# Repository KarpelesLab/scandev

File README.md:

# scandev

A self-contained nuclear quadrupole resonance (NQR) spectrometer: put a
sample in a coil, send a short radio-frequency pulse, and listen for the
faint signal the nuclei send back. The frequency of that signal identifies
the compound, through a sealed container and with no magnet.

The project follows Applied Science's video
[Identify chemicals with radio frequencies - Nuclear Quadrupole Resonance (MRI without magnets)](https://www.youtube.com/watch?v=JO_EHceV9sk),
which builds one around an oscilloscope, a bench amplifier and a passive
transmit/receive network. Here the oscilloscope is replaced by an FPGA, an
ADC and purpose-built boards.

## Status

Early. Nothing has been built or run on hardware yet.

| Part | State |
|------|-------|
| Probe and pulse numbers (`sim/probe.py`) | done |
| Transmit/receive front end in SPICE (`sim/frontend.py`) | passive network modelled |
| Amplifier output network (`sim/pa.py`) | done |
| Schematics of the four boards (`hw/`) | written; KiCad's netlist matches and the rule check passes |
| Layout of the four boards | placed and autorouted; no rule violations, nothing unconnected; not reviewed |
| Parts | every catalogue number checked against JLCPCB; only the SMA connectors and the probe's hand-fitted parts are not chosen |
| Fabrication files (`hw/lib/fab.py`) | generated for all four boards; placement rotations unchecked |
| Gateware core (`gateware/rtl`) | passes simulation, synthesises for `xc7a35t-ftg256`; on hold until a board exists |
| RP2040 firmware, host software | not started |

## Boards

Four boards joined by SMA cables. Each is a pair of Python scripts in
`hw/`: one writes the KiCad schematic, a PDF of it and a BOM, and checks
KiCad's reading of the netlist against the script; the other places the
footprints, routes the board and runs the design rule check.

- **Digital** (`hw/dig`): Xilinx Artix-7 (XC7A35T-FTG256) and an AD9226
  12-bit ADC on one 50 MHz oscillator. An RP2040 with its own USB-C port,
  BOOTSEL and reset buttons loads the FPGA (there is no configuration
  flash) and keeps bitstreams and scan results on a microSD card.
- **Amplifier** (`hw/pa`): a half-bridge switching at the carrier, 3.8 W
  at 12 V into 50 ohm. It is silent when it is not switching, and its rail
  collapses if it is left transmitting. Takes the 12 V input for the system.
- **Receive front end** (`hw/fe`): series crossed diodes towards the
  amplifier, three quarter-wave sections with shunt diodes towards the
  receiver, two low-noise stages with a blanking switch between them.
- **Probe** (`hw/probe`): the tuning and matching capacitors for the
  sample coil, 1 kV parts with pads for hand-fitted variable capacitors,
  and a thermistor for the sample's temperature. Goes in a shielded box
  with the coil.

The amplifier's output network and the front end's quarter-wave sections
are fitted to one frequency. They are fitted for hexamine.

Renders of the current layouts (KiCad's 3D view; parts without a 3D model
in KiCad's library, the FPGA among them, are missing):

| | |
|---|---|
|  Digital |  Amplifier |
|  Receive front end |  Probe |

### Wiring

| From | To | Cable |
|------|----|-------|
| digital `TX HI`, `TX LO` | amplifier `HI IN`, `LO IN` | SMA |
| digital `PA EN` | amplifier `EN` | 2-pin |
| amplifier `TX OUT` | front end `TX IN` | SMA |
| front end `PROBE` | probe `TO FRONT END` | SMA |
| front end `RX OUT` | digital `RX IN` | SMA |
| digital `BLANK` | front end `PWR/BLANK` pins 3-4 | 2-pin |
| amplifier `12V OUT A` | front end `PWR/BLANK` pins 1-2 | 2-pin |
| amplifier `12V OUT B` | digital `12V IN` | 2-pin |
| probe `TEMP` | digital `TEMP` | 2-pin |

The digital board's logic runs from its USB port; 12 V only feeds its ADC.

### Known weak points

- The layouts are autorouted first passes. Nobody has looked at the
  amplifier feedback loops, return paths or the FPGA's supply routing.
- The OPA855 stages are fast enough to oscillate on a careless layout.
- The gateware drives the two bridge inputs as exact complements. The
  driver blocks both-on but adds no dead time; the gateware should.
- The FPGA's supplies come up in no particular order.
- The ADC's 5 V regulator drops 7 V at about 100 mA and will run warm.

## Samples

The video's sodium nitrite is not something to buy casually, so the first
target is **hexamine** (solid camping-fuel tablets): a nitrogen line at
3.306 MHz at room temperature whose signal lasts about 1.5 ms, long enough
that the receiver's dead time after the pulse costs little.

## Layout

```
sim/        design numbers and the ngspice front-end model
hw/         board scripts, generated schematics, PDFs and BOMs
gateware/   Verilog (rtl/), testbench and its Python judge (tb/)
video/      script used to transcribe the reference video for study
```

## Running the checks

```sh
python3 sim/probe.py          # coil, matching, pulse length, ring-down
python3 sim/frontend.py       # needs ngspice
python3 gateware/tb/run_core.py
python3 hw/fe/fe.py           # schematic; likewise pa, dig, probe; needs KiCad 9+
python3 hw/fe/fe_pcb.py --route   # layout; needs freerouting under tools/
python3 hw/lib/checkbom.py hw/*/*-bom.csv
python3 hw/lib/fab.py fe pa probe dig
```

The gateware is simulated and synthesised with
[reticle](https://github.com/KarpelesLab/reticle). `run_core.py` looks for
the binary at `tools/reticle-target/release/reticle`, or wherever the
`RETICLE` environment variable points.

## Safety

The probe coil and the probe board carry several hundred volts of RF
during a pulse. Sodium
nitrite is toxic in gram quantities: keep it in a sealed tube.

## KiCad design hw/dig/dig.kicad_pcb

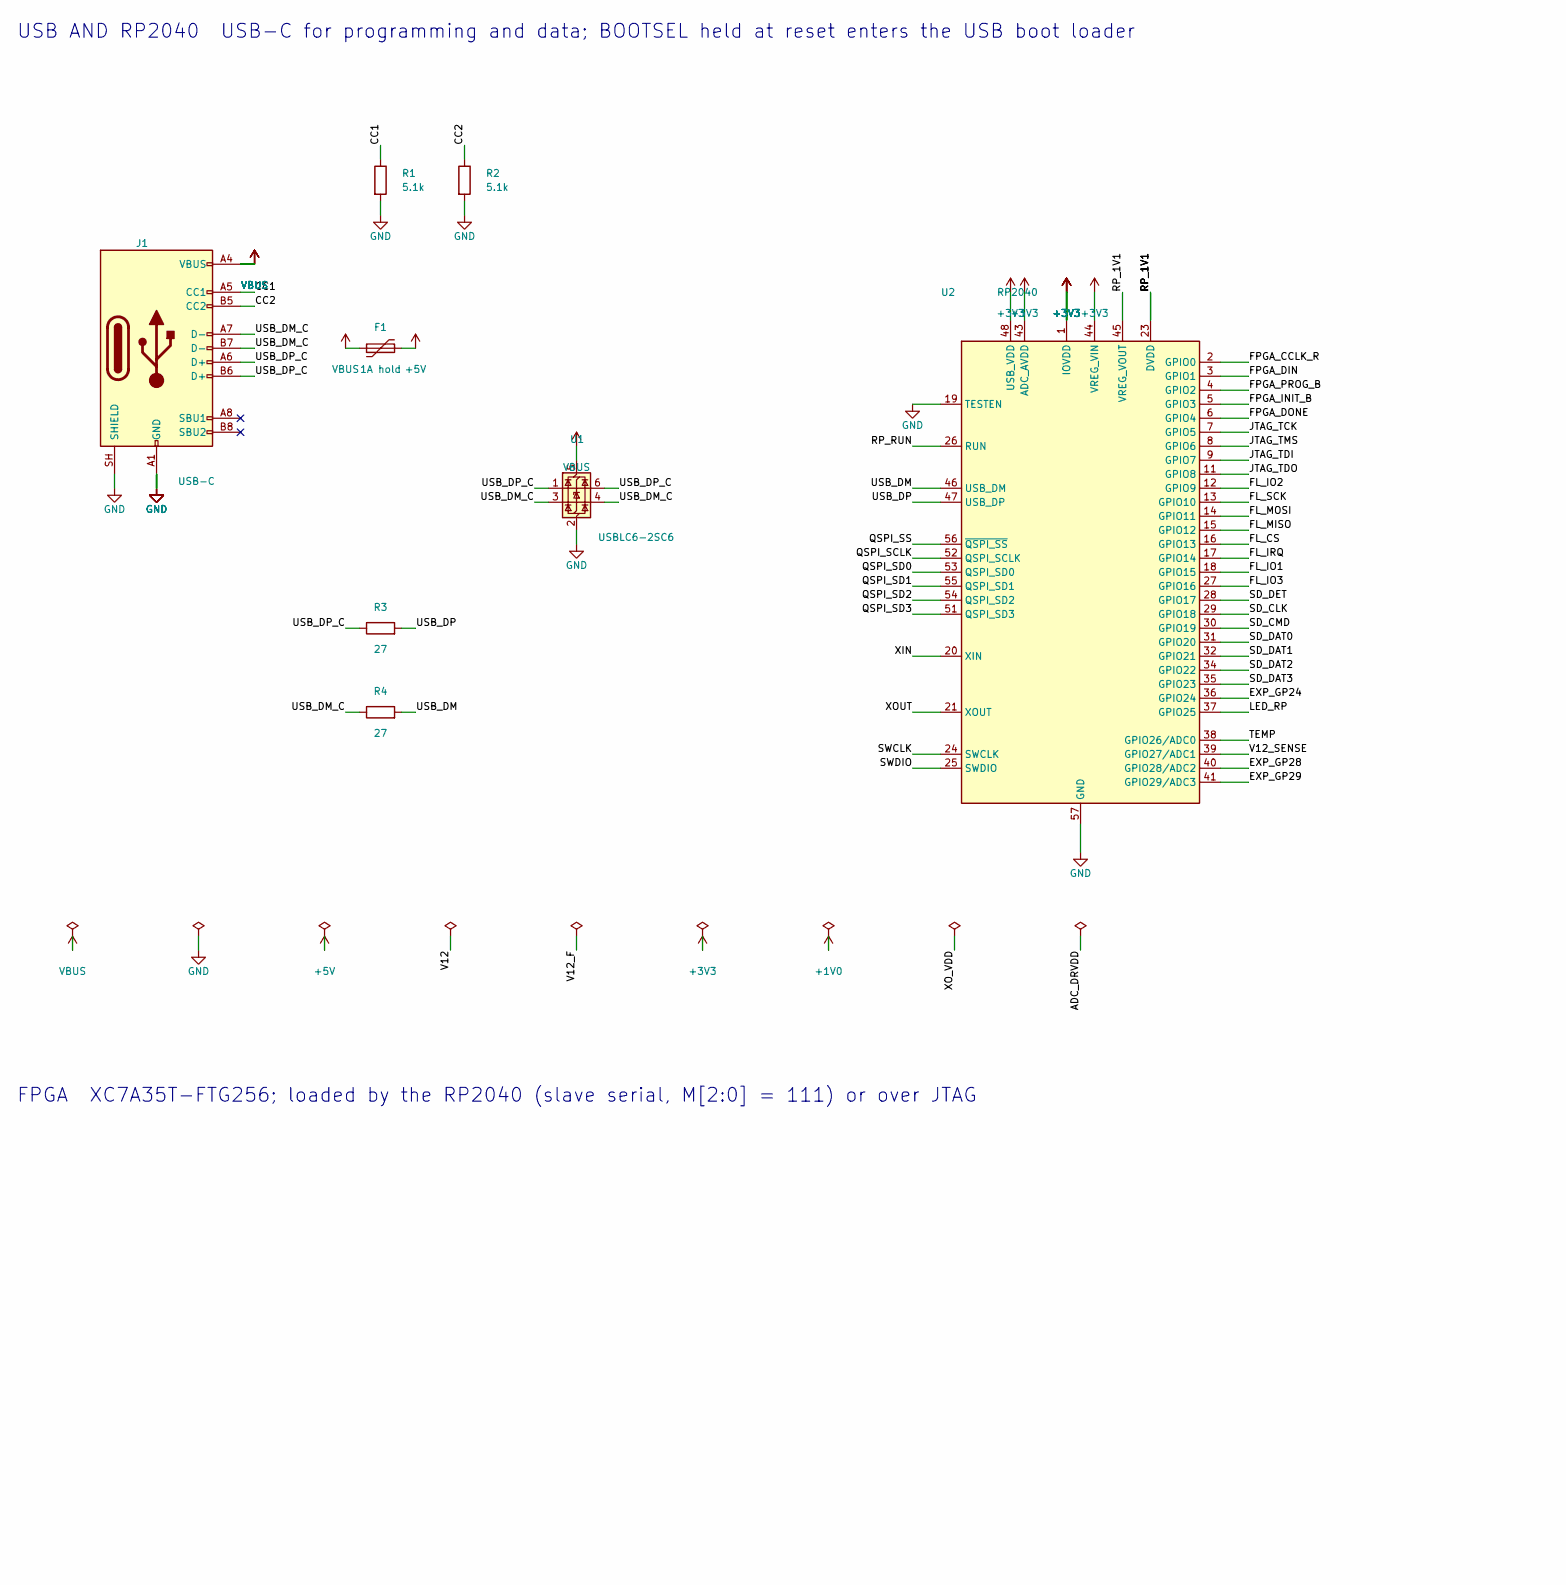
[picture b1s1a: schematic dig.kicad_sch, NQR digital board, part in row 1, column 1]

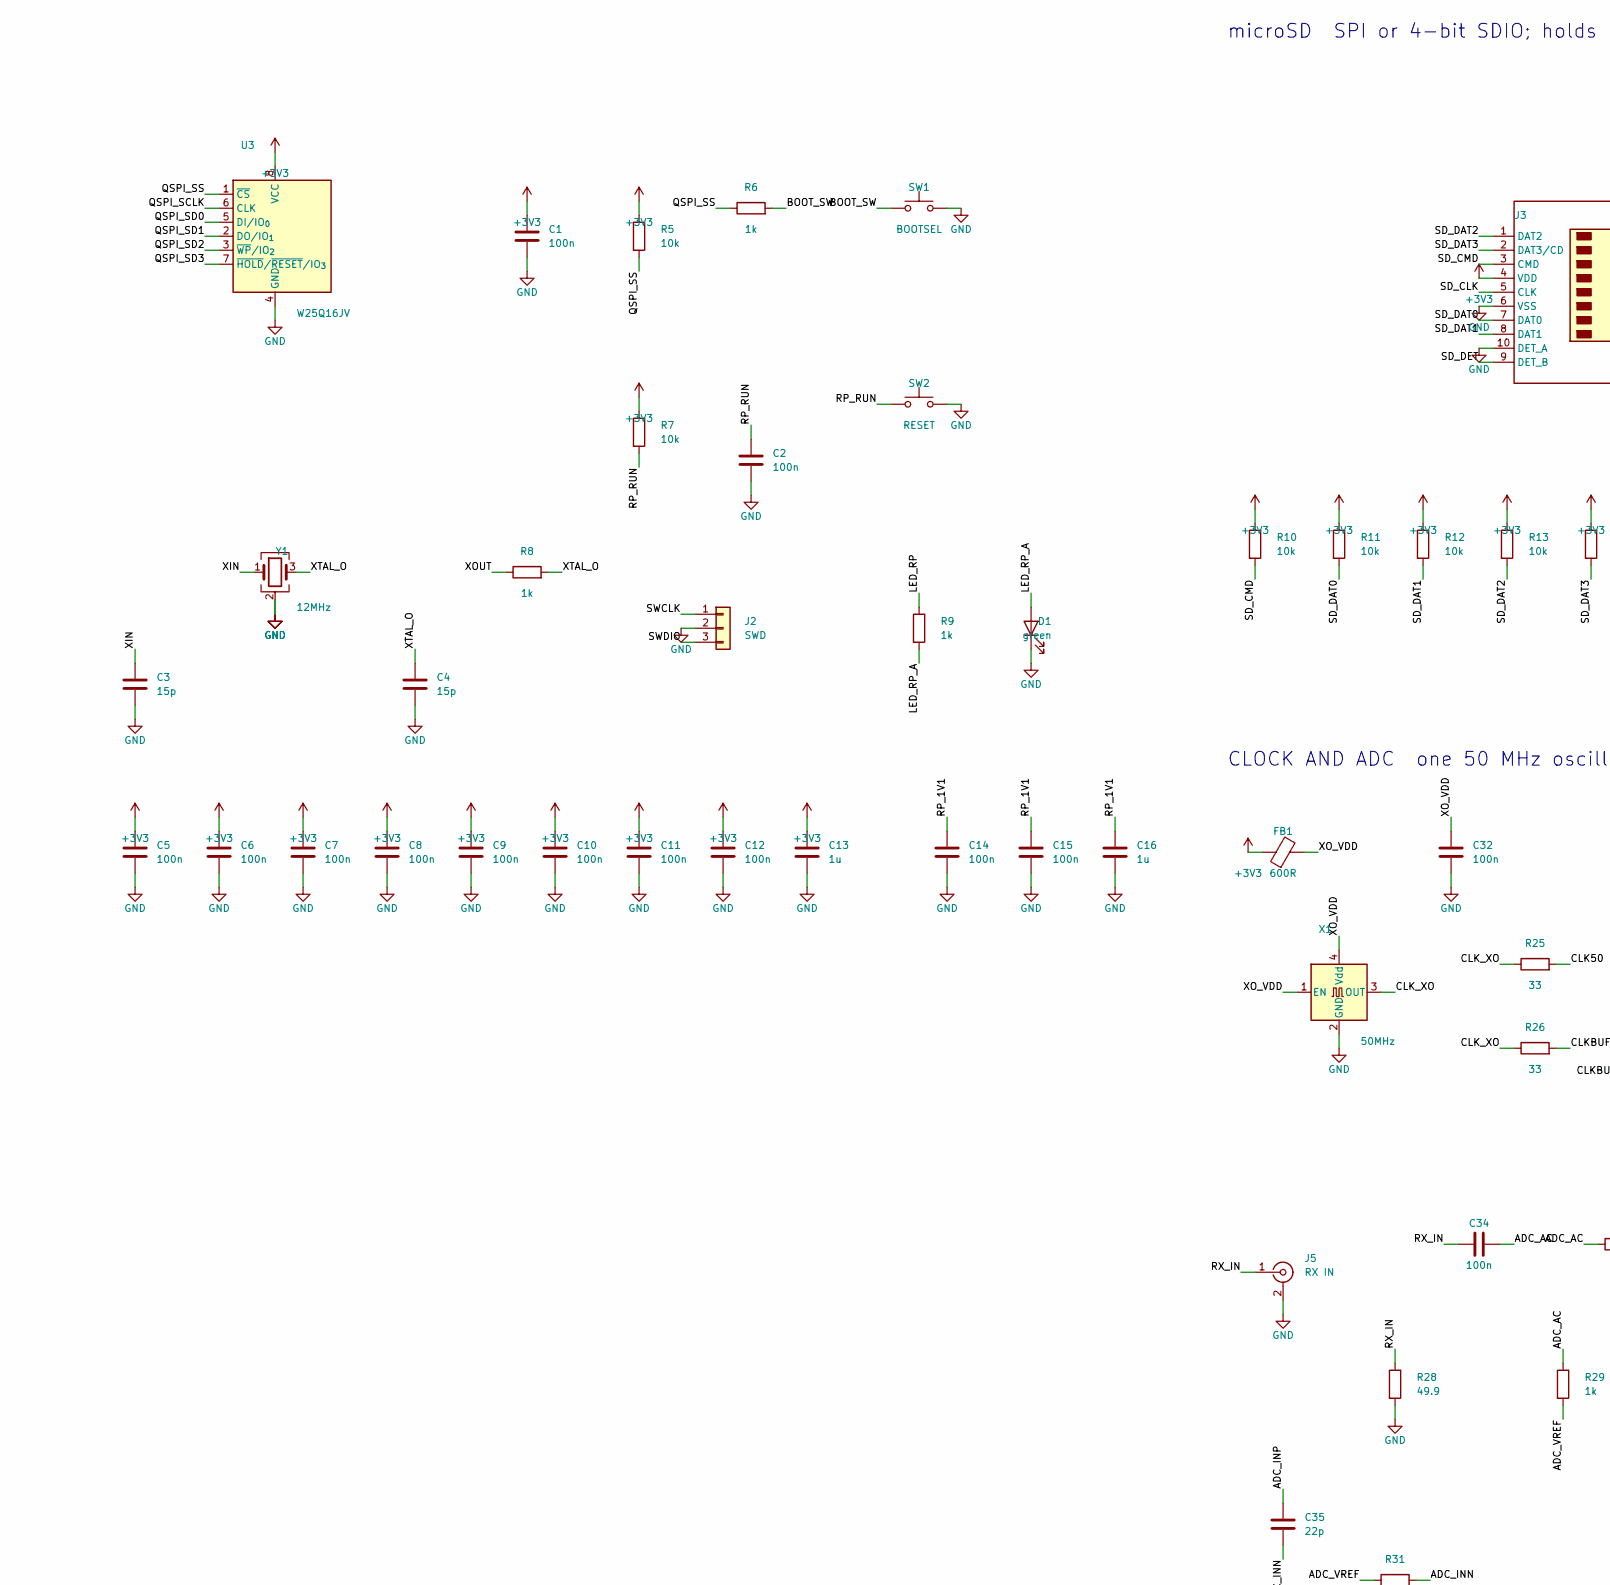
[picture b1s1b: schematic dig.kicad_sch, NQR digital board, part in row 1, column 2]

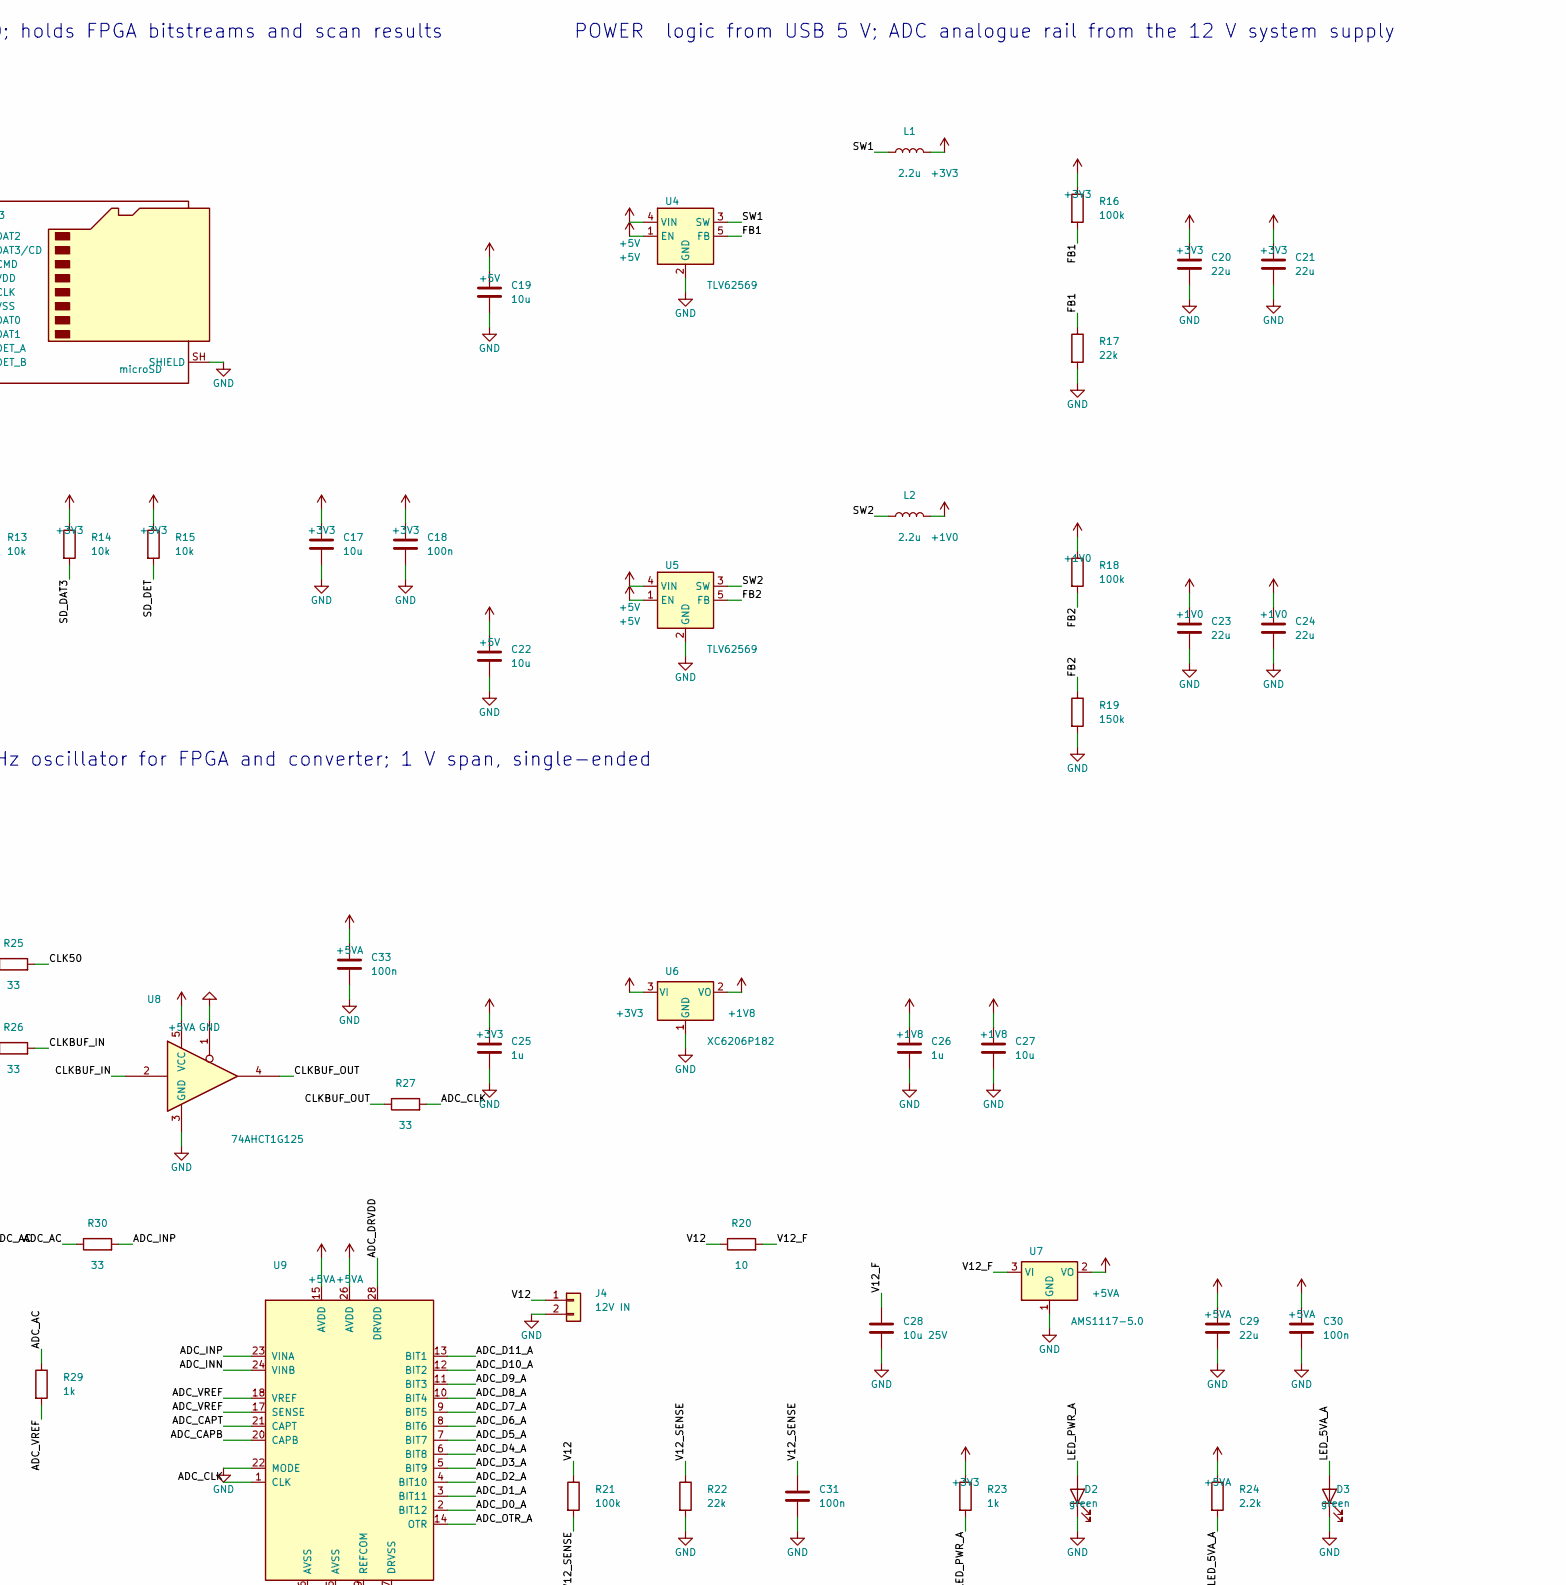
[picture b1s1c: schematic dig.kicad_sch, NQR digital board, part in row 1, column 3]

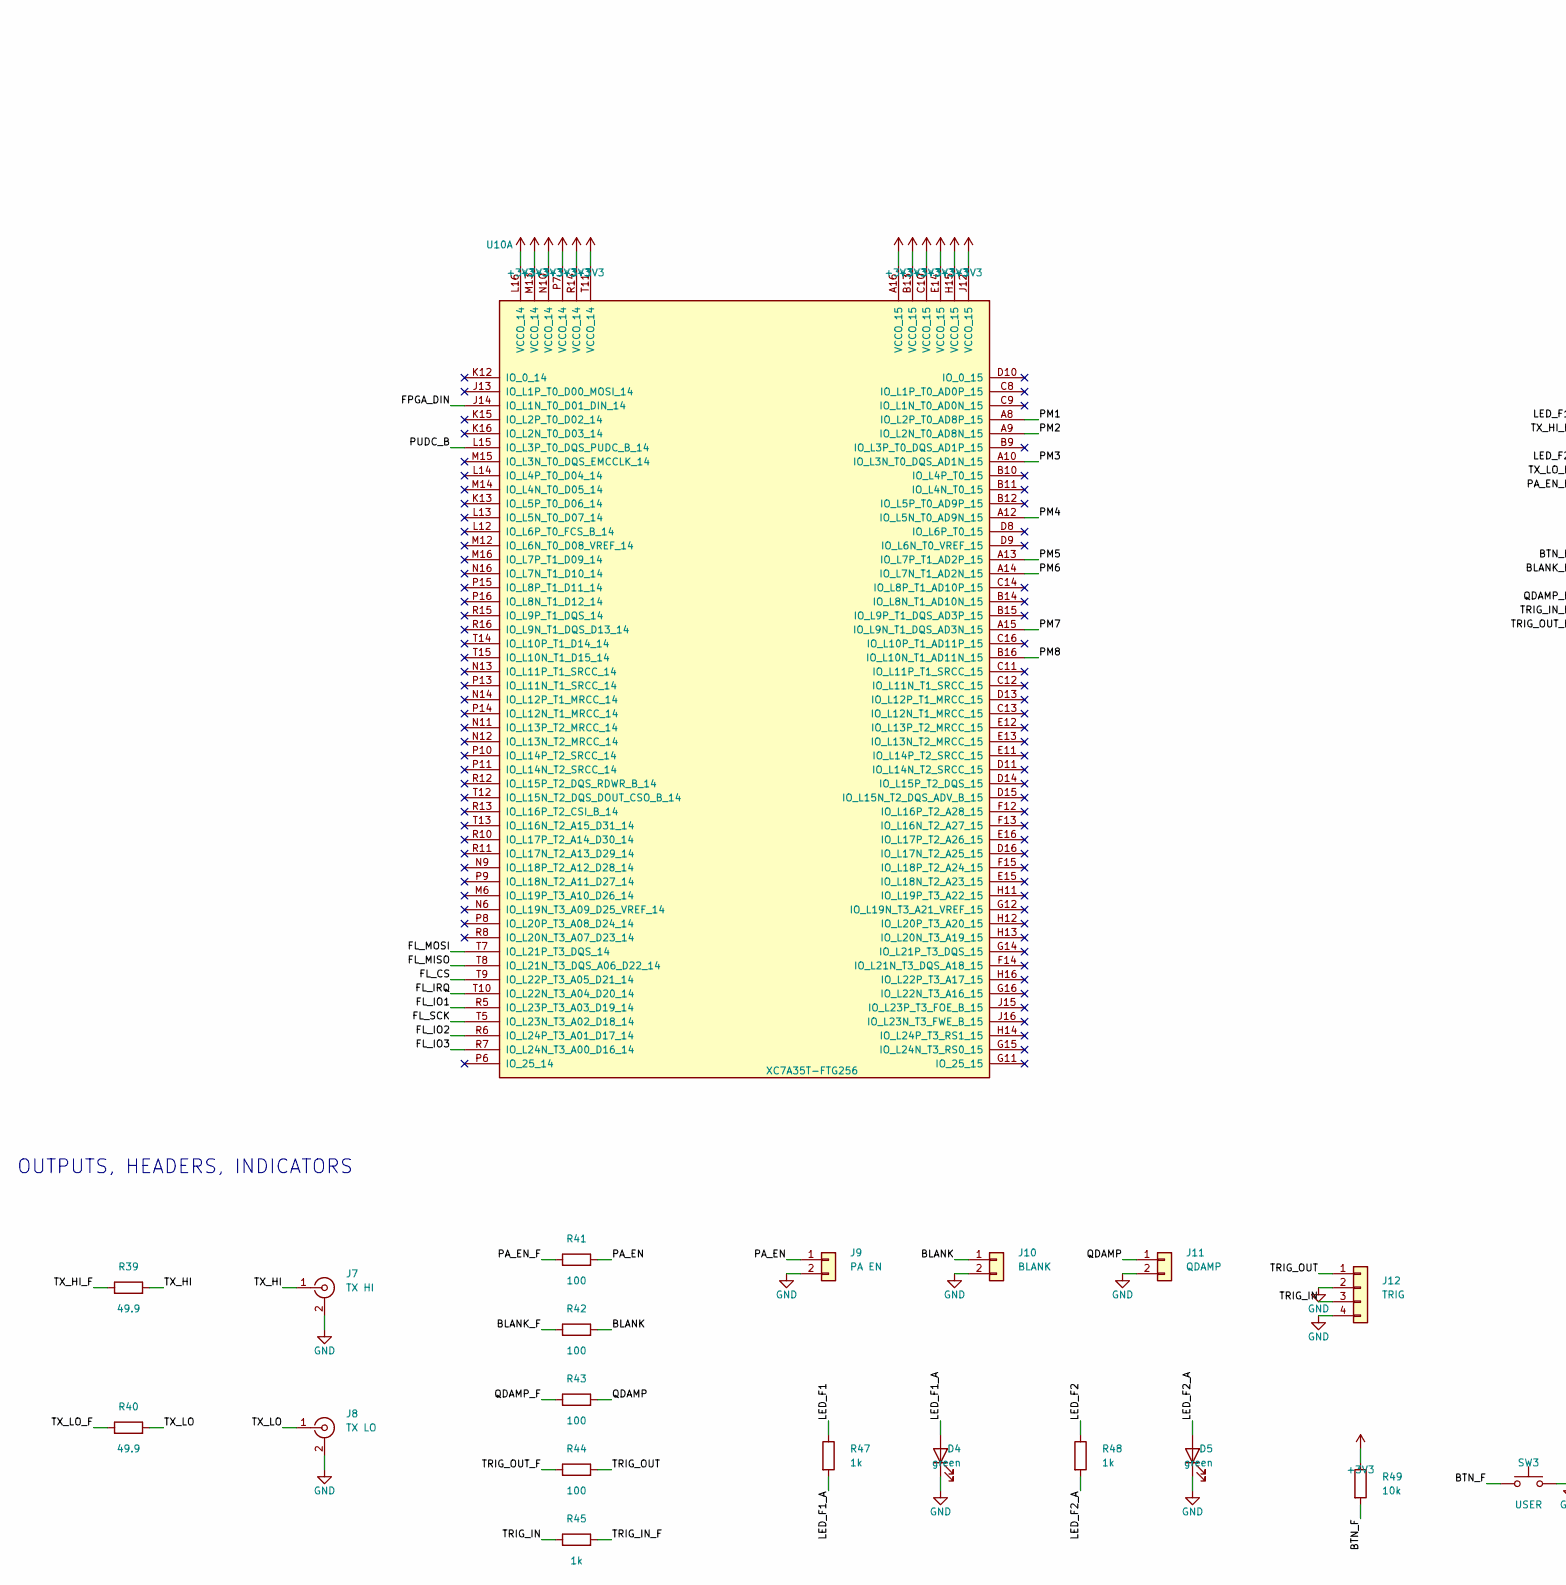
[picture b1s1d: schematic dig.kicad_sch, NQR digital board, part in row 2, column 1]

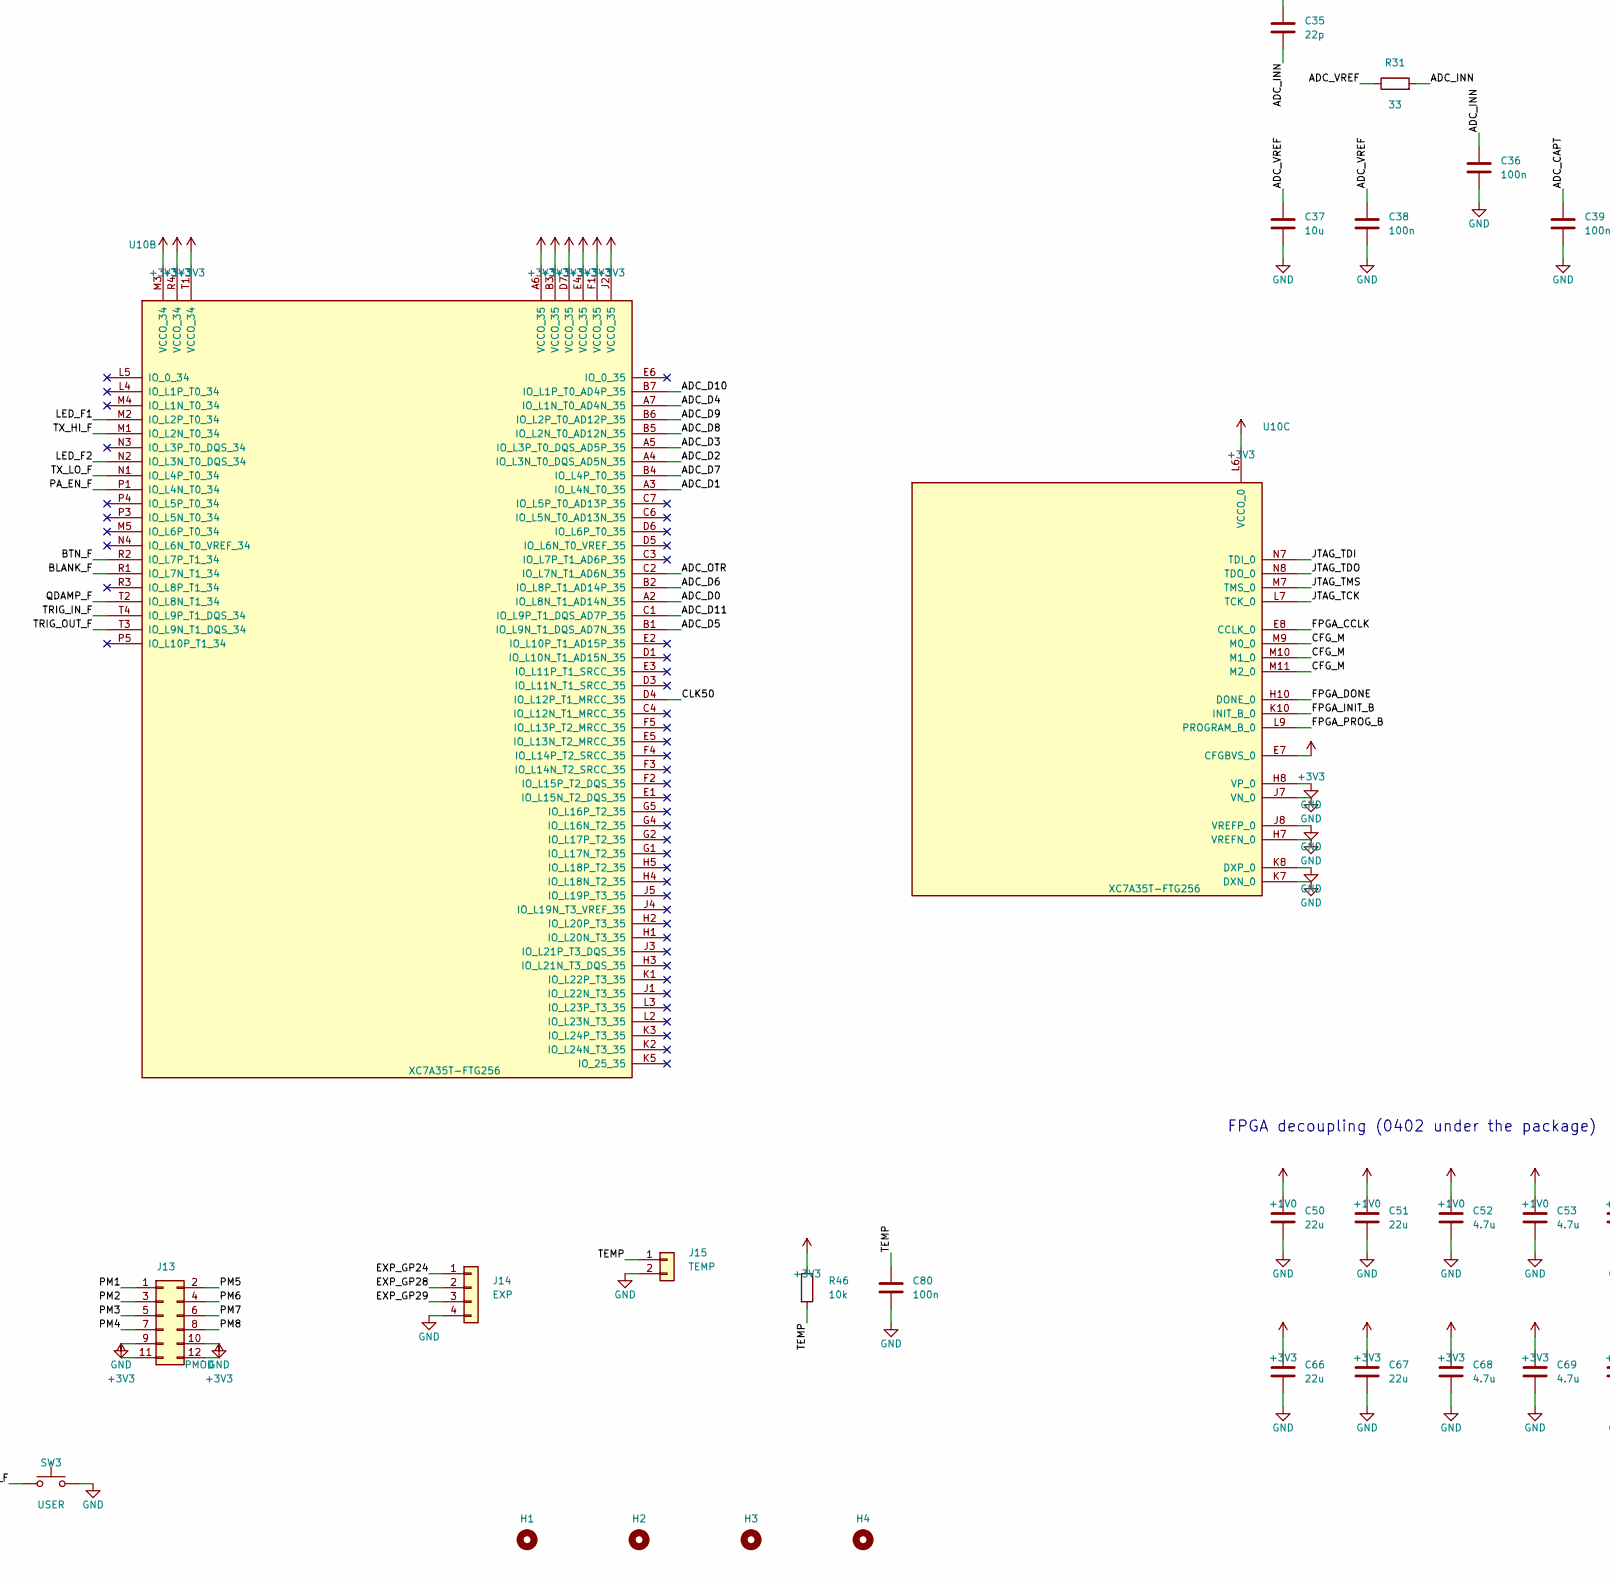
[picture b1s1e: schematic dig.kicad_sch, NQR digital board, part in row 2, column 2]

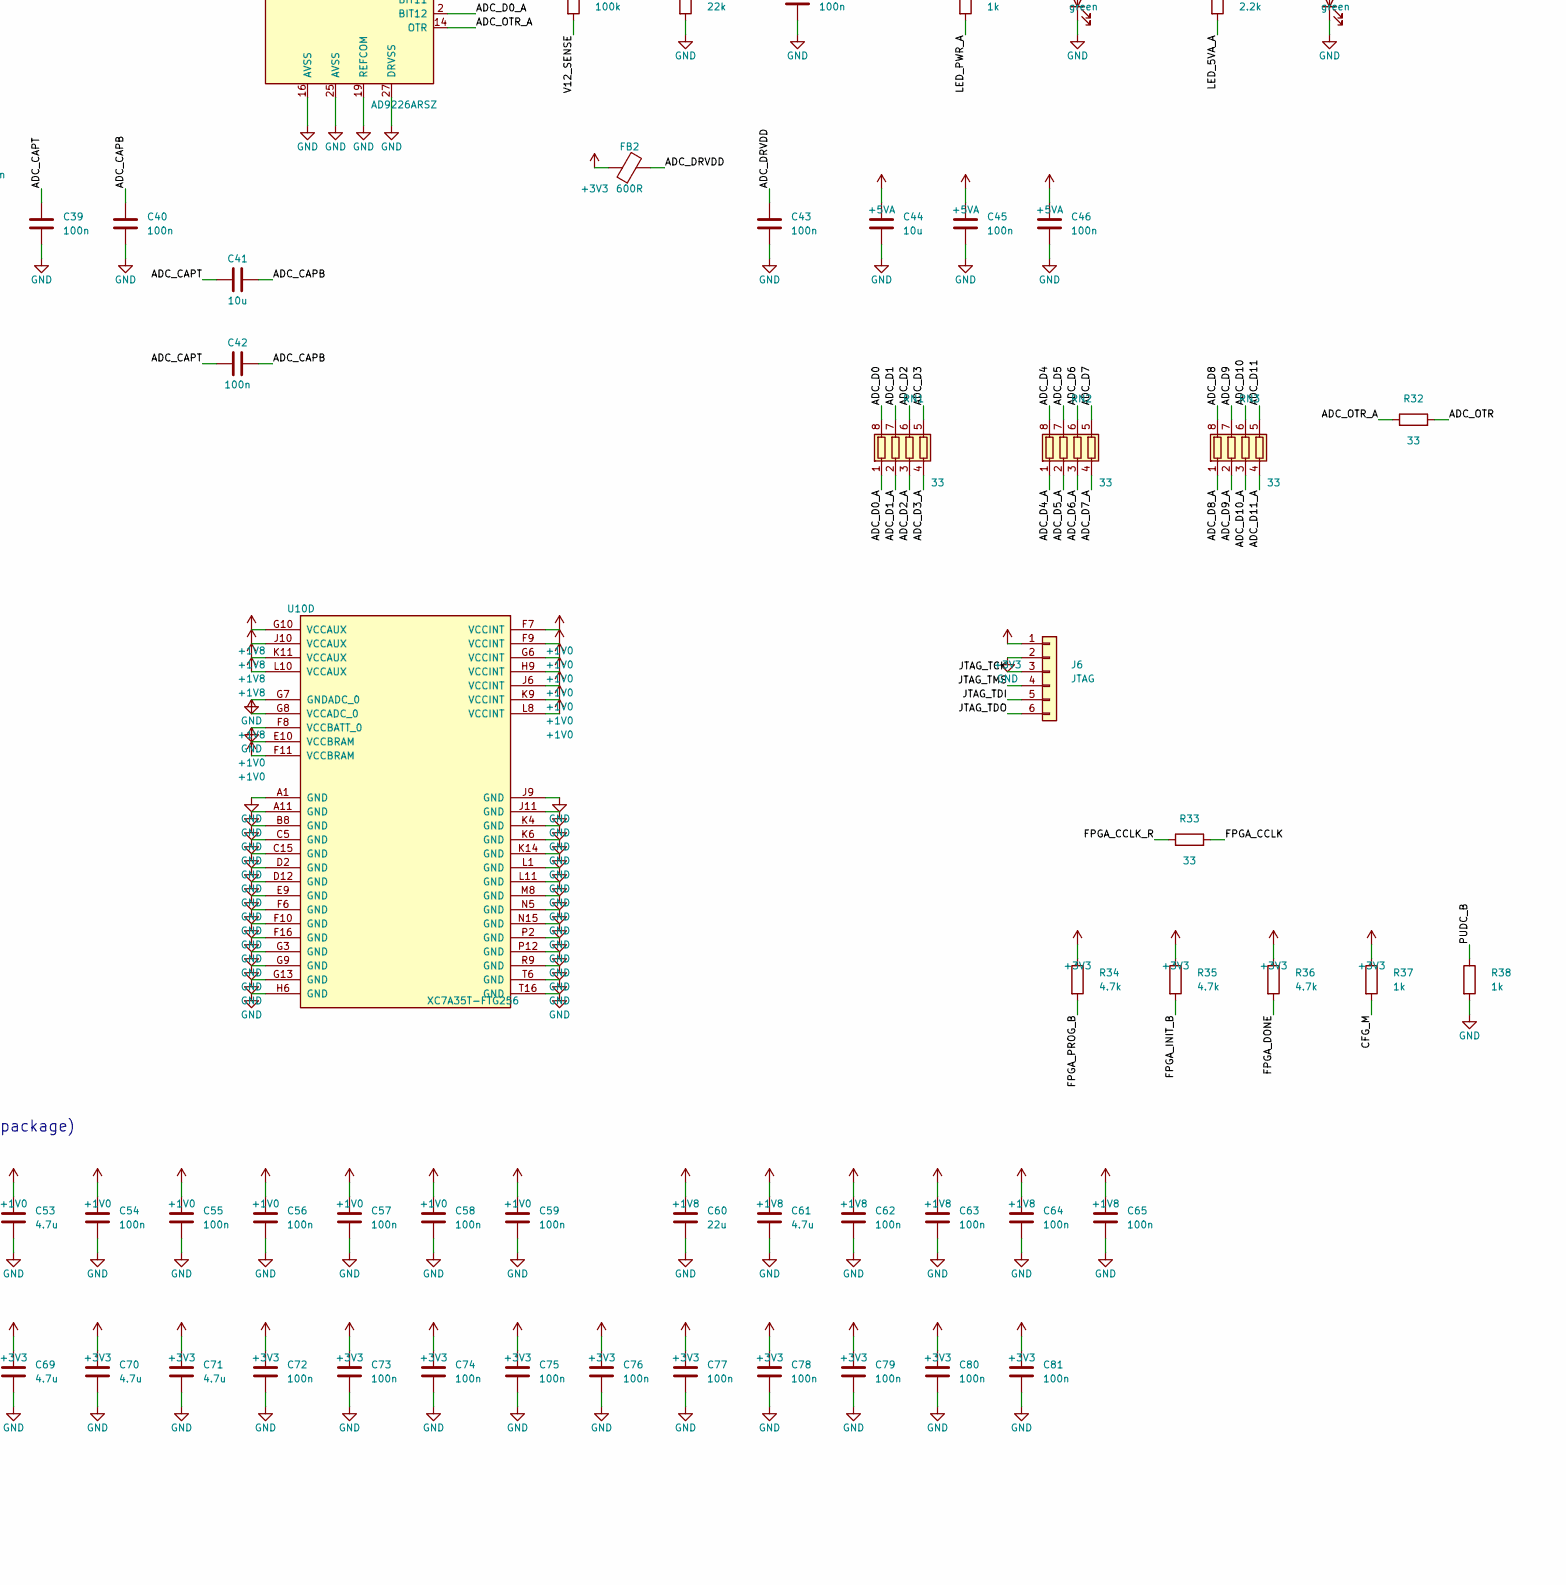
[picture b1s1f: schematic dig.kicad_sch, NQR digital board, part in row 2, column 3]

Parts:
C1, C2, C5, C6, C7, C8, C9, C10, C11, C12, C14, C15, C18, C30, C31, C32, C33, C34, C36, C38, C39, C40, C42, C43, C45, C46: 100n; C_0603_1608Metric; LCSC C14663
C3, C4: 15p; C_0603_1608Metric; LCSC C107037
C13, C16, C25, C26: 1u; C_0603_1608Metric; LCSC C15849
C17, C19, C22, C27, C37, C41, C44: 10u; C_0805_2012Metric; LCSC C15850
C20, C21, C23, C24, C29, C50, C51, C60, C66, C67: 22u; C_0805_2012Metric; LCSC C98190
C28: 10u 25V; C_1206_3216Metric; LCSC C9807
C35: 22p; C_0603_1608Metric; LCSC C525244
C52, C53, C61, C68, C69, C70, C71: 4.7u; C_0805_2012Metric; LCSC C1779
C54, C55, C56, C57, C58, C59, C62, C63, C64, C65, C72, C73, C74, C75, C76, C77, C78, C79, C80, C81: 100n; C_0402_1005Metric; LCSC C1525
D1, D2, D3, D4, D5: green; LED_0603_1608Metric; LCSC C72043
F1: 1A hold; Fuse_1206_3216Metric; MPN SMD1206P100TF; LCSC C20800
FB1, FB2: 600R; L_0603_1608Metric; MPN GZ1608D601TF; LCSC C1002
H1, H2, H3, H4: M3; MountingHole_3.2mm_M3
J1: USB-C; USB_C_Receptacle_HRO_TYPE-C-31-M-12; MPN TYPE-C-31-M-12; LCSC C165948
J2: SWD; PinHeader_1x03_P2.54mm_Vertical
J3: microSD; microSD_HC_Molex_104031-0811; MPN 104031-0811; LCSC C585350
J4: 12V IN; PinHeader_1x02_P2.54mm_Vertical
J5: RX IN; SMA_Samtec_SMA-J-P-H-ST-EM1_EdgeMount
J6: JTAG; PinHeader_1x06_P2.54mm_Vertical
J7: TX HI; SMA_Samtec_SMA-J-P-H-ST-EM1_EdgeMount
J8: TX LO; SMA_Samtec_SMA-J-P-H-ST-EM1_EdgeMount
J9: PA EN; PinHeader_1x02_P2.54mm_Vertical
J10: BLANK; PinHeader_1x02_P2.54mm_Vertical
J11: QDAMP; PinHeader_1x02_P2.54mm_Vertical
J12: TRIG; PinHeader_1x04_P2.54mm_Vertical
J13: PMOD; PinHeader_2x06_P2.54mm_Vertical
J14: EXP; PinHeader_1x04_P2.54mm_Vertical
J15: TEMP; PinHeader_1x02_P2.54mm_Vertical
L1, L2: 2.2u; L_Changjiang_FNR5040S; MPN FNR5040S2R2MT; LCSC C167957
R1, R2: 5.1k; R_0603_1608Metric; LCSC C2907044
R3, R4: 27; R_0603_1608Metric; LCSC C25190
R5, R7, R10, R11, R12, R13, R14, R15, R46, R49: 10k; R_0603_1608Metric; LCSC C25804
R6, R8, R9, R23, R29, R37, R38, R45, R47, R48: 1k; R_0603_1608Metric; LCSC C21190
R16, R18, R21: 100k; R_0603_1608Metric; LCSC C115320
R17, R22: 22k; R_0603_1608Metric; LCSC C114065
R19: 150k; R_0603_1608Metric; LCSC C402995
R20: 10; R_1206_3216Metric; LCSC C2828881
R24: 2.2k; R_0603_1608Metric; LCSC C844925
R25, R26, R27, R30, R31, R32, R33: 33; R_0603_1608Metric; LCSC C23140
R28, R39, R40: 49.9; R_0603_1608Metric; LCSC C23185
R34, R35, R36: 4.7k; R_0603_1608Metric; LCSC C116693
R41, R42, R43, R44: 100; R_0603_1608Metric; LCSC C22775
RN1, RN2, RN3: 33; R_Array_Convex_4x0603; MPN 4D03WGJ0330T5E; LCSC C25508
SW1: BOOTSEL; SW_Push_1P1T_XKB_TS-1187A; MPN TS-1187A-C-C-B; LCSC C318889
SW2: RESET; SW_Push_1P1T_XKB_TS-1187A; MPN TS-1187A-C-C-B; LCSC C318889
SW3: USER; SW_Push_1P1T_XKB_TS-1187A; MPN TS-1187A-C-C-B; LCSC C318889
U1: USBLC6-2SC6; SOT-23-6; MPN USBLC6-2SC6; LCSC C7519
U2: RP2040; QFN-56-1EP_7x7mm_P0.4mm_EP3.2x3.2mm; MPN RP2040; LCSC C2040
U3: W25Q16JV; SOIC-8_5.3x5.3mm_P1.27mm; MPN W25Q16JVSSIQ; LCSC C131025
U4, U5: TLV62569; SOT-23-5; MPN TLV62569DBVR; LCSC C141836
U6: XC6206P182; SOT-23; MPN XC6206P182MR; LCSC C51886219
U7: AMS1117-5.0; SOT-223-3_TabPin2; MPN AMS1117-5.0; LCSC C6187
U8: 74AHCT1G125; SOT-23-5; MPN SN74AHCT1G125DBVR; LCSC C7484
U9: AD9226ARSZ; SSOP-28_5.3x10.2mm_P0.65mm; MPN AD9226ARSZ; LCSC C730053
U10: XC7A35T-FTG256; Xilinx_FTG256; MPN XC7A35T-2FTG256C; LCSC C181716
X1: 50MHz; Oscillator_SMD_Abracon_ASE-4Pin_3.2x2.5mm; MPN SiT8008BI-22-33E-50.000000; LCSC C26267
Y1: 12MHz; Crystal_SMD_3225-4Pin_3.2x2.5mm; MPN X322512MSB4SI; LCSC C9002

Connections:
+1V0: C23.1, C24.1, C50.1, C51.1, C52.1, C53.1, C54.1, C55.1, C56.1, C57.1, C58.1, C59.1, L2.2, R18.1, U10.E10 (VCCBRAM), U10.F7 (VCCINT), U10.F9 (VCCINT), U10.F11 (VCCBRAM), U10.G6 (VCCINT), U10.H9 (VCCINT), U10.J6 (VCCINT), U10.K9 (VCCINT), U10.L8 (VCCINT)
+1V8: C26.1, C27.1, C60.1, C61.1, C62.1, C63.1, C64.1, C65.1, U6.2 (VO), U10.G8 (VCCADC_0), U10.G10 (VCCAUX), U10.J10 (VCCAUX), U10.K11 (VCCAUX), U10.L10 (VCCAUX)
+5V: C19.1, C22.1, F1.2, U4.1 (EN), U4.4 (VIN), U5.1 (EN), U5.4 (VIN)
+5VA: C29.1, C30.1, C33.1, C44.1, C45.1, C46.1, R24.1, U7.2 (VO), U8.5 (VCC), U9.15 (AVDD), U9.26 (AVDD)
ADC_AC: C34.2, R29.1, R30.1
ADC_CAPB: C40.1, C41.2, C42.2, U9.20 (CAPB)
ADC_CAPT: C39.1, C41.1, C42.1, U9.21 (CAPT)
ADC_CLK: R27.2, U9.1 (CLK)
ADC_D0: RN1.8 (R1.2), U10.A2 (IO_L8N_T1_AD14N_35)
ADC_D0_A: RN1.1 (R1.1), U9.2 (BIT12)
ADC_D1: RN1.7 (R2.2), U10.A3 (IO_L4N_T0_35)
ADC_D1_A: RN1.2 (R2.1), U9.3 (BIT11)
ADC_D2: RN1.6 (R3.2), U10.A4 (IO_L3N_T0_DQS_AD5N_35)
ADC_D2_A: RN1.3 (R3.1), U9.4 (BIT10)
ADC_D3: RN1.5 (R4.2), U10.A5 (IO_L3P_T0_DQS_AD5P_35)
ADC_D3_A: RN1.4 (R4.1), U9.5 (BIT9)
ADC_D4: RN2.8 (R1.2), U10.A7 (IO_L1N_T0_AD4N_35)
ADC_D4_A: RN2.1 (R1.1), U9.6 (BIT8)
ADC_D5: RN2.7 (R2.2), U10.B1 (IO_L9N_T1_DQS_AD7N_35)
ADC_D5_A: RN2.2 (R2.1), U9.7 (BIT7)
ADC_D6: RN2.6 (R3.2), U10.B2 (IO_L8P_T1_AD14P_35)
ADC_D6_A: RN2.3 (R3.1), U9.8 (BIT6)
ADC_D7: RN2.5 (R4.2), U10.B4 (IO_L4P_T0_35)
ADC_D7_A: RN2.4 (R4.1), U9.9 (BIT5)
ADC_D8: RN3.8 (R1.2), U10.B5 (IO_L2N_T0_AD12N_35)
ADC_D8_A: RN3.1 (R1.1), U9.10 (BIT4)
ADC_D9: RN3.7 (R2.2), U10.B6 (IO_L2P_T0_AD12P_35)
ADC_D9_A: RN3.2 (R2.1), U9.11 (BIT3)
ADC_D10: RN3.6 (R3.2), U10.B7 (IO_L1P_T0_AD4P_35)
ADC_D10_A: RN3.3 (R3.1), U9.12 (BIT2)
ADC_D11: RN3.5 (R4.2), U10.C1 (IO_L9P_T1_DQS_AD7P_35)
ADC_D11_A: RN3.4 (R4.1), U9.13 (BIT1)
ADC_DRVDD: C43.1, FB2.2, U9.28 (DRVDD)
ADC_INN: C35.2, C36.1, R31.2, U9.24 (VINB)
ADC_INP: C35.1, R30.2, U9.23 (VINA)
ADC_OTR: R32.2, U10.C2 (IO_L7N_T1_AD6N_35)
ADC_OTR_A: R32.1, U9.14 (OTR)
ADC_VREF: C37.1, C38.1, R29.2, R31.1, U9.17 (SENSE), U9.18 (VREF)
BLANK: J10.1, R42.2
BLANK_F: R42.1, U10.R1 (IO_L7N_T1_34)
BOOT_SW: R6.2, SW1.1
BTN_F: R49.2, SW3.1, U10.R2 (IO_L7P_T1_34)
CC1: J1.A5 (CC1), R1.1
CC2: J1.B5 (CC2), R2.1
CFG_M: R37.2, U10.M9 (M0_0), U10.M10 (M1_0), U10.M11 (M2_0)
CLK50: R25.2, U10.D4 (IO_L12P_T1_MRCC_35)
CLKBUF_IN: R26.2, U8.2
CLKBUF_OUT: R27.1, U8.4
CLK_XO: R25.1, R26.1, X1.3 (OUT)
EXP_GP24: J14.1, U2.36 (GPIO24)
EXP_GP28: J14.2, U2.40 (GPIO28/ADC2)
EXP_GP29: J14.3, U2.41 (GPIO29/ADC3)
FB1: R16.2, R17.1, U4.5 (FB)
FB2: R18.2, R19.1, U5.5 (FB)
FL_CS: U2.16 (GPIO13), U10.T9 (IO_L22P_T3_A05_D21_14)
FL_IO1: U2.18 (GPIO15), U10.R5 (IO_L23P_T3_A03_D19_14)
FL_IO2: U2.12 (GPIO9), U10.R6 (IO_L24P_T3_A01_D17_14)
FL_IO3: U2.27 (GPIO16), U10.R7 (IO_L24N_T3_A00_D16_14)
FL_IRQ: U2.17 (GPIO14), U10.T10 (IO_L22N_T3_A04_D20_14)
FL_MISO: U2.15 (GPIO12), U10.T8 (IO_L21N_T3_DQS_A06_D22_14)
FL_MOSI: U2.14 (GPIO11), U10.T7 (IO_L21P_T3_DQS_14)
FL_SCK: U2.13 (GPIO10), U10.T5 (IO_L23N_T3_A02_D18_14)
FPGA_CCLK: R33.2, U10.E8 (CCLK_0)
FPGA_CCLK_R: R33.1, U2.2 (GPIO0)
FPGA_DIN: U2.3 (GPIO1), U10.J14 (IO_L1N_T0_D01_DIN_14)
FPGA_DONE: R36.2, U2.6 (GPIO4), U10.H10 (DONE_0)
FPGA_INIT_B: R35.2, U2.5 (GPIO3), U10.K10 (INIT_B_0)
FPGA_PROG_B: R34.2, U2.4 (GPIO2), U10.L9 (PROGRAM_B_0)
GND: C1.2, C2.2, C3.2, C4.2, C5.2, C6.2, C7.2, C8.2, C9.2, C10.2, C11.2, C12.2, C13.2, C14.2, C15.2, C16.2, C17.2, C18.2, C19.2, C20.2, C21.2, C22.2, C23.2, C24.2, C25.2, C26.2, C27.2, C28.2, C29.2, C30.2, C31.2, C32.2, C33.2, C36.2, C37.2, C38.2, C39.2, C40.2, C43.2, C44.2, C45.2, C46.2, C50.2, C51.2, C52.2, C53.2, C54.2, C55.2, C56.2, C57.2, C58.2, C59.2, C60.2, C61.2, C62.2, C63.2, C64.2, C65.2, C66.2, C67.2, C68.2, C69.2, C70.2, C71.2, C72.2, C73.2, C74.2, C75.2, C76.2, C77.2, C78.2, C79.2, C80.2, C81.2, D1.1 (K), D2.1 (K), D3.1 (K), D4.1 (K), D5.1 (K), J1.A1 (GND), J1.A12 (GND), J1.B1 (GND), J1.B12 (GND), J1.SH (SHIELD), J2.2, J3.6 (VSS), J3.10 (DET_A), J3.SH (SHIELD), J4.2, J5.2 (Ext), J6.2, J7.2 (Ext), J8.2 (Ext), J9.2, J10.2, J11.2, J12.2, J12.4, J13.9, J13.10, J14.4, J15.2, R1.2, R2.2, R17.2, R19.2, R22.2, R28.2, R38.2, SW1.2, SW2.2, SW3.2, U1.2 (GND), U2.19 (TESTEN), U2.57 (GND), U3.4 (GND), U4.2 (GND), U5.2 (GND), U6.1 (GND), U7.1 (GND), U8.1, U8.3 (GND), U9.16 (AVSS), U9.19 (REFCOM), U9.22 (MODE), U9.25 (AVSS), U9.27 (DRVSS), U10.A1 (GND), U10.A11 (GND), U10.B8 (GND), U10.C5 (GND), U10.C15 (GND), U10.D2 (GND), U10.D12 (GND), U10.E9 (GND), U10.F6 (GND), U10.F8 (VCCBATT_0), U10.F10 (GND), U10.F16 (GND), U10.G3 (GND)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
JTAG_TCK: J6.3, U2.7 (GPIO5), U10.L7 (TCK_0)
JTAG_TDI: J6.5, U2.9 (GPIO7), U10.N7 (TDI_0)
JTAG_TDO: J6.6, U2.11 (GPIO8), U10.N8 (TDO_0)
JTAG_TMS: J6.4, U2.8 (GPIO6), U10.M7 (TMS_0)
LED_5VA_A: D3.2 (A), R24.2
LED_F1: R47.1, U10.M2 (IO_L2P_T0_34)
LED_F1_A: D4.2 (A), R47.2
LED_F2: R48.1, U10.N2 (IO_L3N_T0_DQS_34)
LED_F2_A: D5.2 (A), R48.2
LED_PWR_A: D2.2 (A), R23.2
LED_RP: R9.1, U2.37 (GPIO25)
LED_RP_A: D1.2 (A), R9.2
PA_EN: J9.1, R41.2
PA_EN_F: R41.1, U10.P1 (IO_L4N_T0_34)
PM1: J13.1, U10.A8 (IO_L2P_T0_AD8P_15)
PM2: J13.3, U10.A9 (IO_L2N_T0_AD8N_15)
PM3: J13.5, U10.A10 (IO_L3N_T0_DQS_AD1N_15)
PM4: J13.7, U10.A12 (IO_L5N_T0_AD9N_15)
PM5: J13.2, U10.A13 (IO_L7P_T1_AD2P_15)
PM6: J13.4, U10.A14 (IO_L7N_T1_AD2N_15)
PM7: J13.6, U10.A15 (IO_L9N_T1_DQS_AD3N_15)
PM8: J13.8, U10.B16 (IO_L10N_T1_AD11N_15)
PUDC_B: R38.1, U10.L15 (IO_L3P_T0_DQS_PUDC_B_14)
QDAMP: J11.1, R43.2
QDAMP_F: R43.1, U10.T2 (IO_L8N_T1_34)
QSPI_SCLK: U2.52 (QSPI_SCLK), U3.6 (CLK)
QSPI_SD0: U2.53 (QSPI_SD0), U3.5 (DI/IO_{0})
QSPI_SD1: U2.55 (QSPI_SD1), U3.2 (DO/IO_{1})
QSPI_SD2: U2.54 (QSPI_SD2), U3.3 (~WP/IO_{2})
QSPI_SD3: U2.51 (QSPI_SD3), U3.7 (~HOLD/~RESET/IO_{3})
QSPI_SS: R5.2, R6.1, U2.56 (~QSPI_SS), U3.1 (~CS)
RP_1V1: C14.1, C15.1, C16.1, U2.23 (DVDD), U2.45 (VREG_VOUT), U2.50 (DVDD)
RP_RUN: C2.1, R7.2, SW2.1, U2.26 (RUN)
RX_IN: C34.1, J5.1 (In), R28.1
SD_CLK: J3.5 (CLK), U2.29 (GPIO18)
SD_CMD: J3.3 (CMD), R10.2, U2.30 (GPIO19)
SD_DAT0: J3.7 (DAT0), R11.2, U2.31 (GPIO20)
SD_DAT1: J3.8 (DAT1), R12.2, U2.32 (GPIO21)
SD_DAT2: J3.1 (DAT2), R13.2, U2.34 (GPIO22)
SD_DAT3: J3.2 (DAT3/CD), R14.2, U2.35 (GPIO23)
SD_DET: J3.9 (DET_B), R15.2, U2.28 (GPIO17)
SW1: L1.1, U4.3 (SW)
SW2: L2.1, U5.3 (SW)
SWCLK: J2.1, U2.24 (SWCLK)
SWDIO: J2.3, U2.25 (SWDIO)
TRIG_IN: J12.3, R45.1
TRIG_IN_F: R45.2, U10.T4 (IO_L9P_T1_DQS_34)
TRIG_OUT: J12.1, R44.2
TRIG_OUT_F: R44.1, U10.T3 (IO_L9N_T1_DQS_34)
TX_HI: J7.1 (In), R39.2
TX_HI_F: R39.1, U10.M1 (IO_L2N_T0_34)
TX_LO: J8.1 (In), R40.2
TX_LO_F: R40.1, U10.N1 (IO_L4P_T0_34)
USB_DM: R4.2, U2.46 (USB_DM)
USB_DM_C: J1.A7 (D-), J1.B7 (D-), R4.1, U1.3 (I/O2), U1.4 (I/O2)
USB_DP: R3.2, U2.47 (USB_DP)
USB_DP_C: J1.A6 (D+), J1.B6 (D+), R3.1, U1.1 (I/O1), U1.6 (I/O1)
V12: J4.1, R20.1, R21.1
V12_F: C28.1, R20.2, U7.3 (VI)
V12_SENSE: C31.1, R21.2, R22.1, U2.39 (GPIO27/ADC1)
VBUS: F1.1, J1.A4 (VBUS), J1.A9 (VBUS), J1.B4 (VBUS), J1.B9 (VBUS), U1.5 (VBUS)
XIN: C3.1, U2.20 (XIN), Y1.1
XOUT: R8.1, U2.21 (XOUT)
XO_VDD: C32.1, FB1.2, X1.1 (EN), X1.4 (Vdd)
XTAL_O: C4.1, R8.2, Y1.3

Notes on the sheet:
USB AND RP2040 USB-C for programming and data; BOOTSEL held at reset enters the USB boot loader
microSD SPI or 4-bit SDIO; holds FPGA bitstreams and scan results
POWER logic from USB 5 V; ADC analogue rail from the 12 V system supply
CLOCK AND ADC one 50 MHz oscillator for FPGA and converter; 1 V span, single-ended
FPGA XC7A35T-FTG256; loaded by the RP2040 (slave serial, M[2:0] = 111) or over JTAG
FPGA decoupling (0402 under the package)
OUTPUTS, HEADERS, INDICATORS

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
